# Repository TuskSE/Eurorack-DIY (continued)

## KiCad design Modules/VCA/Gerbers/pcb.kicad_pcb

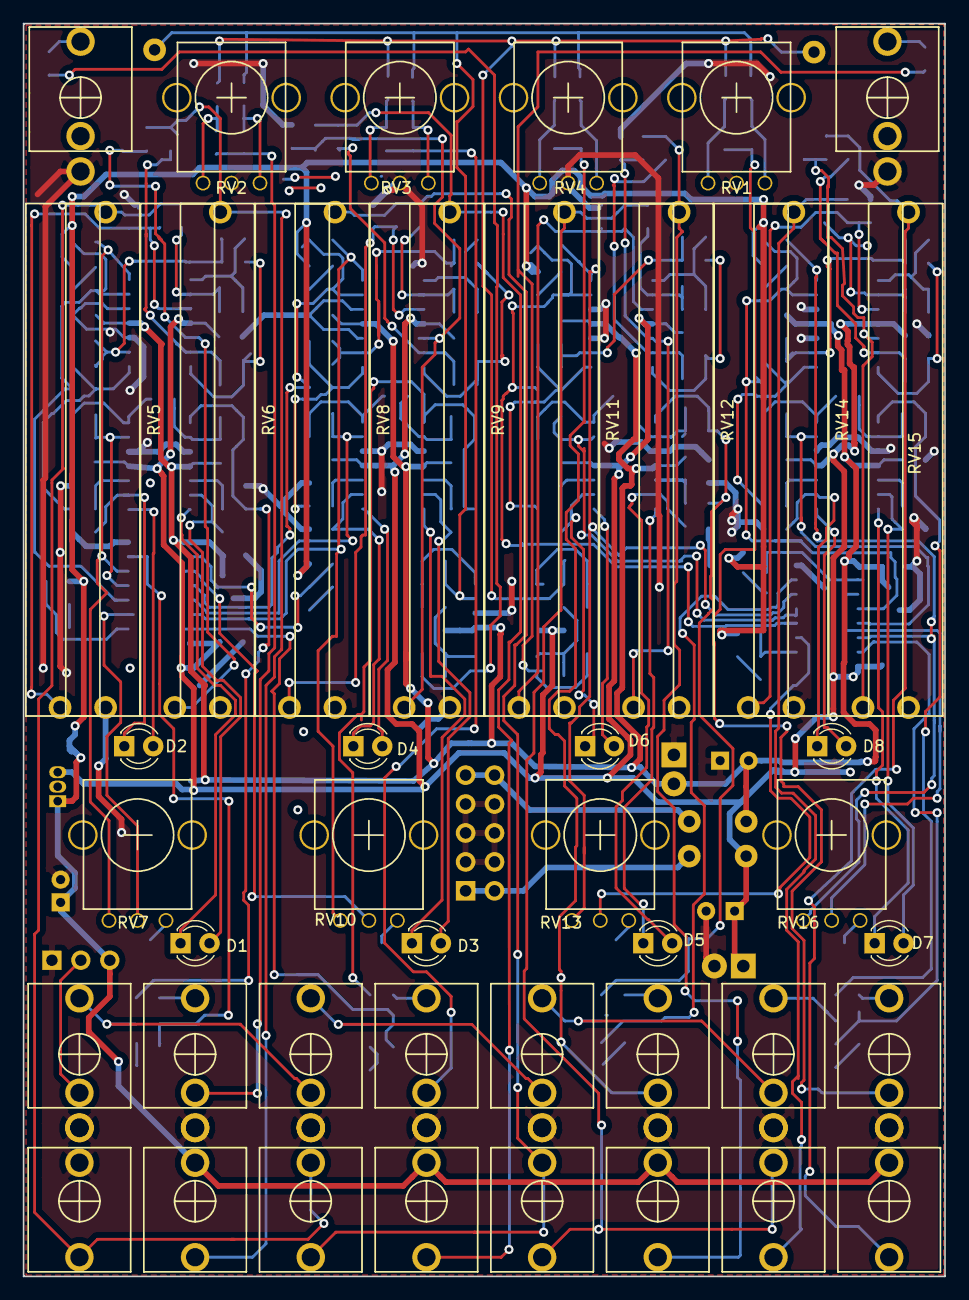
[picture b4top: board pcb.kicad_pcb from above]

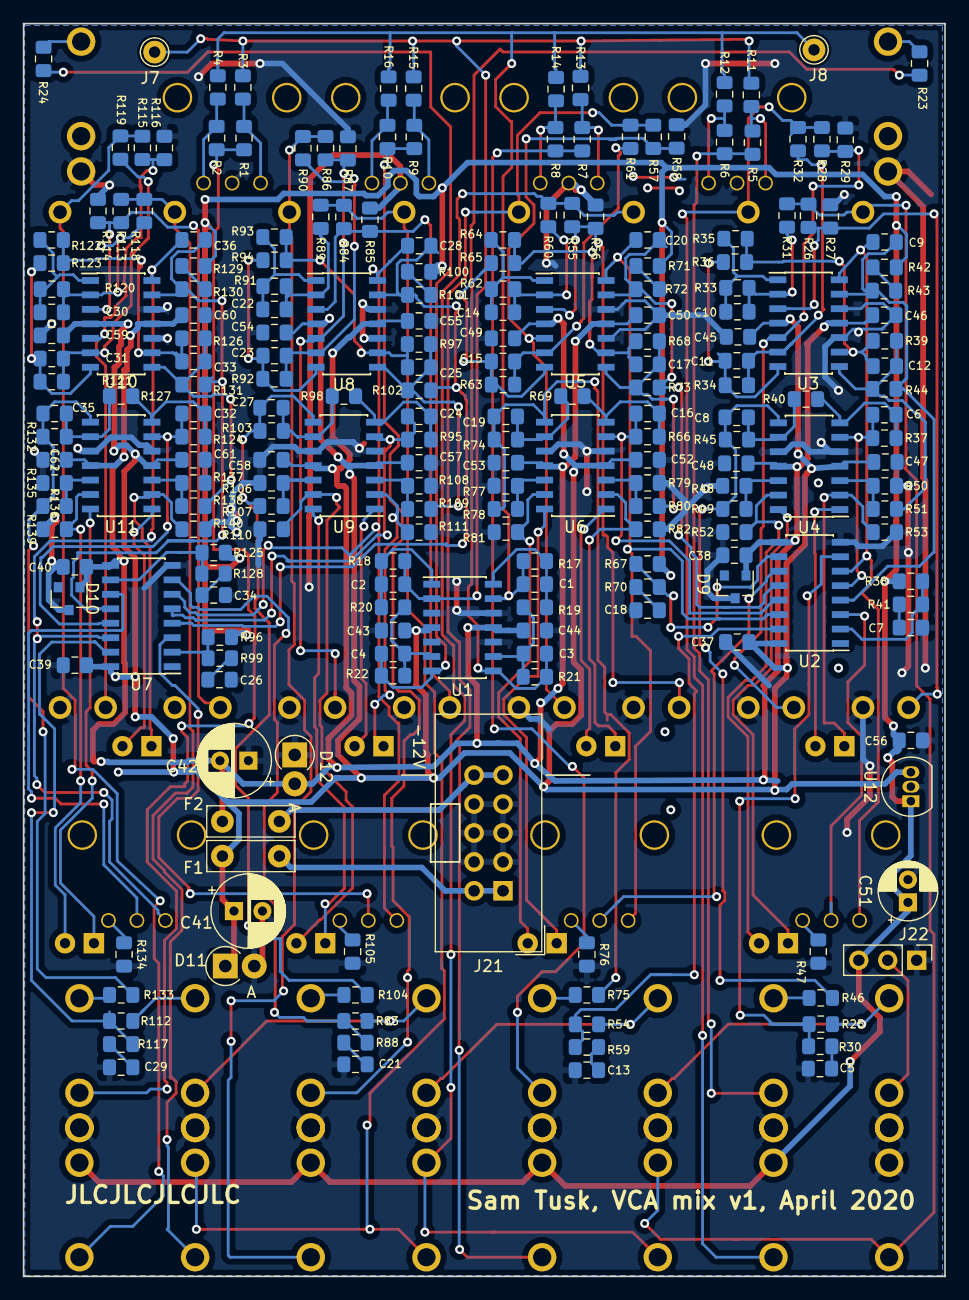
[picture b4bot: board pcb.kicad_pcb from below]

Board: 2 copper layers, 80.9 x 110.0 mm, 266 parts (224 on the bottom side), 153 nets.

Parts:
C1, C2, C3, C4, C6, C9, C10, C11, C12, C14, C15, C16, C17, C20, C22, C23, C24, C25, C28, C30, C31, C32, C33, C36: 47p; C_0805_2012Metric_Pad1.15x1.40mm_HandSolder_SmallTxt
C5, C7, C13, C18, C21, C26, C29, C34: 560p; C_0805_2012Metric_Pad1.15x1.40mm_HandSolder_SmallTxt
C8, C19, C27, C35: 100p; C_0805_2012Metric_Pad1.15x1.40mm_HandSolder_SmallTxt
C37, C38, C39, C40, C43, C44, C45, C46, C47, C48, C49, C50, C52, C53, C54, C55, C56, C57, C58, C59, C60, C61, C62: 100nF; C_0805_2012Metric_Pad1.15x1.40mm_HandSolder_SmallTxt
C41, C42: 100uF; CP_Radial_D6.3mm_P2.50mm
C51: 10uF; CP_Radial_D5.0mm_P2.00mm
D1, D2, D3, D4, D5, D6, D7, D8: Tayda A-1076; LED_D3.0mm
D9, D10: BAT54C; SOT-23
D11, D12: 1N4001; D_DO-41_SOD81_P2.54mm_Vertical_AnodeUp
F1: Polyfuse 250mA (A-1391); C_Disc_D7.5mm_W2.5mm_P5.00mm
F2: Polyfuse 250mA; C_Disc_D7.5mm_W2.5mm_P5.00mm
J1, J2, J3, J4, J5, J6, J9, J10, J11, J12, J13, J14, J15, J16, J17, J18, J19, J20: PJ301M-12; PJ301M-12-MoreMetal
J7, J8: Conn_01x01; Pin_D1.0mm_L10.0mm
J21: EURO_PWR_2x5; Eurorack_power_header
J22: Conn_01x03_Male; PinHeader_1x03_P2.54mm_Vertical
R1, R2, R3, R4, R5, R6, R7, R8, R9, R10, R11, R12, R13, R14, R15, R16: 15k; R_0805_2012Metric_Pad1.15x1.40mm_HandSolder_smallText
R17, R18: 51k; R_0805_2012Metric_Pad1.15x1.40mm_HandSolder_smallText
R19, R20, R21, R22, R25, R31, R32, R33, R34, R35, R36, R37, R39, R54, R60, R61, R62, R63, R64, R65, R66, R68, R83, R89, R90, R91, R92, R93, R94, R95, R97, R112, R118, R119, R120, R121, R122, R123, R124, R126: 100k; R_0805_2012Metric_Pad1.15x1.40mm_HandSolder_smallText
R23, R24, R30, R41, R46, R59, R70, R75, R88, R99, R104, R117, R128, R133: 470R; R_0805_2012Metric_Pad1.15x1.40mm_HandSolder_smallText
R26, R27, R28, R29, R38, R44, R55, R56, R57, R58, R67, R73, R84, R85, R86, R87, R96, R102, R113, R114, R115, R116, R125, R131: 47k; R_0805_2012Metric_Pad1.15x1.40mm_HandSolder_smallText
R40, R45, R69, R74, R98, R103, R127, R132: 4.7k; R_0805_2012Metric_Pad1.15x1.40mm_HandSolder_smallText
R42, R43, R71, R72, R100, R101, R129, R130: 10M; R_0805_2012Metric_Pad1.15x1.40mm_HandSolder_smallText
R47, R76, R105, R134: 11k; R_0805_2012Metric_Pad1.15x1.40mm_HandSolder_smallText
R48, R49, R50, R51, R77, R78, R79, R80, R106, R107, R108, R109, R135, R136, R137, R138: 1M; R_0805_2012Metric_Pad1.15x1.40mm_HandSolder_smallText
R52, R53, R81, R82, R110, R111, R139, R140: 660R; R_0805_2012Metric_Pad1.15x1.40mm_HandSolder_smallText
RV1, RV2, RV3, RV4: 10k; SongHuei9mmPot
RV5, RV6, RV8, RV9, RV11, RV12, RV14, RV15: 100k; Tayda A-1629 Slide Pot_30mm
RV7, RV10, RV13, RV16: 100k; SongHuei9mmPot
U1, U3, U4, U5, U6, U8, U9, U10, U11: TL074; SOIC-14_3.9x8.7mm_P1.27mm
U2, U7: V2164M; SOIC-16_3.9x9.9mm_P1.27mm
U12: LM78L05_TO92; TO-92_Inline

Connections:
+12V: C37.1, C39.1, C41.1, C43.2, C45.2, C47.2, C49.2, C52.2, C54.2, C57.2, C59.2, C61.2, D11.1, F1.1, U1.4, U2.16, U3.4, U4.4, U5.4, U6.4, U7.16, U8.4, U9.4, U10.4, U11.4, U12.3
-12V: C38.2, C40.2, C42.2, C44.1, C46.1, C48.1, C50.1, C53.1, C55.1, C58.1, C60.1, C62.1, D9.1, D10.1, D12.2, F2.1, U1.11, U2.9, U3.11, U4.11, U5.11, U6.11, U7.9, U8.11, U9.11, U10.11, U11.11
/MixOutL: J1.3, R23.1
/MixOutR: J2.3, R24.1
/PanA: R6.1, R12.2, RV2.3
/PanB: R8.1, R14.2, RV3.3
/PanC: R10.1, R16.2, RV4.3
/PanD: R2.1, R4.2, RV1.3
/Power/+12V_in: F1.2, J21.1, J21.2
/Power/-12V_in: F2.2, J21.9, J21.10
/VCA-A/A_cvLED: D2.2, U4.1
/VCA-A/A_outLED: D1.1, U4.14
/VCA-A/CVinA2: J4.3, R28.1, R32.2, RV6.3
/VCA-A/OutA: J6.3, R46.1
/VCA-B/B_cvLED: D4.2, U6.1
/VCA-B/B_outLED: D3.1, U6.14
/VCA-B/CVinB2: J10.3, R57.1, R61.2, RV9.3
/VCA-B/OutB: J12.3, R75.1
/VCA-C/CVinC2: J14.3, R86.1, R90.2, RV12.3
/VCA-C/C_cvLED: D6.2, U9.1
/VCA-C/C_outLED: D5.1, U9.14
/VCA-C/OutA: J16.3, R104.1
/VCA-D/CVinD2: J18.3, R115.1, R119.2, RV15.3
/VCA-D/D_cvLED: D8.2, U11.1
/VCA-D/D_outLED: D7.1, U11.14
/VCA-D/OutB: J20.3, R133.1
CVinA1: J3.3, J9.2, R26.1, R31.2, RV5.3
CVinA1_norm: C5.2, C7.2, C13.2, C18.2, C21.2, C26.2, C29.2, C34.2, C37.2, C38.1, C39.2, C40.1, C41.2, C42.1, C43.1, C44.2, C45.1, C46.2, C47.1, C48.2, C49.1, C50.2, C51.2, C52.1, C53.2, C54.1, C55.2, C56.2, C57.1, C58.2, C59.1, C60.2, C61.1, C62.2, D9.3, D10.3, D11.2, D12.1, J1.1, J2.1, J3.1, J3.2, J4.1, J5.1, J6.1, J9.1, J10.1, J11.1, J12.1, J13.1, J14.1, J15.1, J16.1, J17.1, J18.1, J19.1, J20.1, J21.3, J21.4, J21.5, J21.6, J21.7, J21.8, J22.1, R27.2, R29.2, R47.1, R48.2, R50.2, R52.1, R53.1, R56.2, R58.2, R76.1, R77.2, R79.2, R81.1, R82.1, R85.2, R87.2, R105.1, R106.2, R108.2, R110.1, R111.1, R114.2, R116.2, R134.1, R135.2, R137.2, R139.1, R140.1, RV1.2, RV2.2, RV3.2, RV4.2, RV5.1, RV6.1, RV8.1, RV9.1, RV11.1, RV12.1, RV14.1, RV15.1, U1.3, U1.5, U1.10, U1.12, U2.8, U3.10, U3.12, U4.5, U4.10, U5.10, U5.12, U6.5, U6.10, U7.8, U8.10, U8.12, U9.5, U9.10, U10.10, U10.12, U11.5, U11.10, U12.2
CVinA2_norm: C51.1, C56.1, J4.2, J10.2, J14.2, J18.2, J22.3, R38.2, R42.2, R67.2, R71.2, R96.2, R100.2, R125.2, R129.2, U12.1
CVinB1: J9.3, J13.2, R55.1, R60.2, RV8.3
CVinC1: J13.3, J17.2, R84.1, R89.2, RV11.3
CVinD1: J17.3, R113.1, R118.2, RV14.3
InA: J5.3, J11.2, R25.2
InA_norm: J5.2, J22.2
InB: J11.3, J15.2, R54.2
InC: J15.3, J19.2, R83.2
InD: J19.3, R112.2
MixBusL: C1.2, J8.1, R4.1, R12.1, R14.1, R16.1, R17.1, U1.13
MixBusR: C2.2, J7.1, R3.2, R11.2, R13.2, R15.2, R18.1, U1.2
unnamed: C1.1, R17.2, R19.1, U1.14
unnamed: C2.1, R18.2, R20.1, U1.1
unnamed: C3.1, R21.2, R23.2, U1.8
unnamed: C3.2, R19.2, R21.1, U1.9
unnamed: C4.1, R22.2, R24.2, U1.7
unnamed: C4.2, R20.2, R22.1, U1.6
unnamed: C5.1, R30.2
unnamed: C6.1, R37.1, R40.2, U4.7
unnamed: C6.2, R37.2, U2.5, U4.6
unnamed: C7.1, R41.2
unnamed: C8.1, R45.1, R46.2, R49.1, U4.8
unnamed: C8.2, R40.1, R45.2, U4.9
unnamed: C9.1, RV7.1, U2.6, U3.14
unnamed: C9.2, R43.1, R44.2, U2.4, U3.13
unnamed: C10.1, R33.1, R35.2, U3.1
unnamed: C10.2, R31.1, R33.2, U3.2
unnamed: C11.1, R34.1, R36.2, U3.7
unnamed: C11.2, R32.1, R34.2, U3.6
unnamed: C12.1, R39.1, R44.1, R51.1, U3.8
unnamed: C12.2, R35.1, R36.1, R39.2, U3.9
unnamed: C13.1, R59.2
unnamed: C14.1, R62.1, R64.2, U5.1
unnamed: C14.2, R60.1, R62.2, U5.2
unnamed: C15.1, R63.1, R65.2, U5.7
unnamed: C15.2, R61.1, R63.2, U5.6
unnamed: C16.1, R66.1, R69.2, U6.7
unnamed: C16.2, R66.2, U2.13, U6.6
unnamed: C17.1, R68.1, R73.1, R80.1, U5.8
unnamed: C17.2, R64.1, R65.1, R68.2, U5.9
unnamed: C18.1, R70.2
unnamed: C19.1, R74.1, R75.2, R78.1, U6.8
unnamed: C19.2, R69.1, R74.2, U6.9
unnamed: C20.1, RV10.1, U2.14, U5.14
unnamed: C20.2, R72.1, R73.2, U2.12, U5.13
unnamed: C21.1, R88.2
unnamed: C22.1, R91.1, R93.2, U8.1
unnamed: C22.2, R89.1, R91.2, U8.2
unnamed: C23.1, R92.1, R94.2, U8.7
unnamed: C23.2, R90.1, R92.2, U8.6
unnamed: C24.1, R95.1, R98.2, U9.7
unnamed: C24.2, R95.2, U7.5, U9.6
unnamed: C25.1, R97.1, R102.1, R109.1, U8.8
unnamed: C25.2, R93.1, R94.1, R97.2, U8.9
unnamed: C26.1, R99.2
unnamed: C27.1, R103.1, R104.2, R107.1, U9.8
unnamed: C27.2, R98.1, R103.2, U9.9
unnamed: C28.1, RV13.1, U7.6, U8.14
unnamed: C28.2, R101.1, R102.2, U7.4, U8.13
unnamed: C29.1, R117.2
unnamed: C30.1, R120.1, R122.2, U10.1
unnamed: C30.2, R118.1, R120.2, U10.2
unnamed: C31.1, R121.1, R123.2, U10.7
unnamed: C31.2, R119.1, R121.2, U10.6
unnamed: C32.1, R124.1, R127.2, U11.7
unnamed: C32.2, R124.2, U7.13, U11.6
unnamed: C33.1, R126.1, R131.1, R138.1, U10.8
unnamed: C33.2, R122.1, R123.1, R126.2, U10.9
unnamed: C34.1, R128.2
unnamed: C35.1, R132.1, R133.2, R136.1, U11.8
unnamed: C35.2, R127.1, R132.2, U11.9
unnamed: C36.1, RV16.1, U7.14, U10.14
unnamed: C36.2, R130.1, R131.2, U7.12, U10.13
unnamed: D1.2, R52.2, U4.13
unnamed: D2.1, R53.2, U4.2
unnamed: D3.2, R81.2, U6.13
unnamed: D4.1, R82.2, U6.2
unnamed: D5.2, R110.2, U9.13
unnamed: D6.1, R111.2, U9.2
unnamed: D7.2, R139.2, U11.13
unnamed: D8.1, R140.2, U11.2
unnamed: R1.2, R3.1, RV1.1
unnamed: R5.2, R11.1, RV2.1
unnamed: R7.2, R13.1, RV3.1
unnamed: R9.2, R15.1, RV4.1
unnamed: R25.1, R30.1, U2.7
unnamed: R26.2, R27.1, RV5.2, U3.3
unnamed: R28.2, R29.1, RV6.2, U3.5
unnamed: R38.1, R41.1, U2.2
unnamed: R42.1, R43.2
unnamed: R47.2, RV7.3
unnamed: R48.1, R49.2, U4.12
unnamed: R50.1, R51.2, U4.3
unnamed: R54.1, R59.1, U2.15
unnamed: R55.2, R56.1, RV8.2, U5.3
unnamed: R57.2, R58.1, RV9.2, U5.5
unnamed: R67.1, R70.1, U2.10
unnamed: R71.1, R72.2
unnamed: R76.2, RV10.3
unnamed: R77.1, R78.2, U6.12
unnamed: R79.1, R80.2, U6.3
unnamed: R83.1, R88.1, U7.7
unnamed: R84.2, R85.1, RV11.2, U8.3
unnamed: R86.2, R87.1, RV12.2, U8.5
unnamed: R96.1, R99.1, U7.2
unnamed: R100.1, R101.2
unnamed: R105.2, RV13.3
unnamed: R106.1, R107.2, U9.12
unnamed: R108.1, R109.2, U9.3
unnamed: R112.1, R117.1, U7.15
unnamed: R113.2, R114.1, RV14.2, U10.3
unnamed: R115.2, R116.1, RV15.2, U10.5
unnamed: R125.1, R128.1, U7.10
unnamed: R129.1, R130.2
unnamed: R134.2, RV16.3
unnamed: R135.1, R136.2, U11.12
unnamed: R137.1, R138.2, U11.3
unnamed: RV7.2, U2.3
unnamed: RV10.2, U2.11
unnamed: RV13.2, U7.3
unnamed: RV16.2, U7.11
OutA_norm: J6.2, R5.1, R6.2
OutB_norm: J12.2, R7.1, R8.2
OutC_norm: J16.2, R9.1, R10.2
OutD_norm: J20.2, R1.1, R2.2
